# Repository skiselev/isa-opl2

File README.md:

# isa-opl2

ISA OPL2 Card

## Introduction

ISA OPL2 Card is a sound card based on Yamaha OPL2 chip, officially known as YM3812. This card is compatible with the AdLib Music Synthesizer Card that was very popular in late 80's - early 90's.

## Hardware Documentation

### Schematic and PCB Layout

[Schematic - Version 1.2](KiCad/ISA_OPL2-Schematic-1.2.pdf)

[PCB Layout - Version 1.2](KiCad/ISA_OPL2-Board-1.2.pdf)

### Bill of Materials

Component Type     | Reference  | Description                                                | Quantity | Possible Sources and Notes
------------------ | ---------- | ---------------------------------------------------------- | -------- | --------------------------
PCB                |            | ISA OPL2 Version 1.2 PCB                                   | 1        | [Todd Goodman](https://retrobrewcomputers.org/doku.php?id=boardinventory) or your favorite PCB manufacturer
Integrated Circuit | U1         | 74LS245                                                    | 1        | Mouser 595-SN74LS245N
Integrated Circuit | U2, U3     | 74LS138                                                    | 2        | Mouser 595-SN74LS138N
Integrated Circuit | U4         | 74LS74                                                     | 1        | Mouser 595-SN74LS74AN
Integrated Circuit | U5         | 74LS04                                                     | 1        | Mouser 595-SN74LS04N
Integrated Circuit | U6         | YM3812                                                     | 1        | eBay
Integrated Circuit | U7         | YM3014B                                                    | 1        | eBay
Integrated Circuit | U8         | RC4136                                                     | 1        | Mouser 595-RC4136N
Integrated Circuit | U9         | LM386-3                                                    | 1        | Mouser 926-LM386N-3/NOPB
Transistor         | Q1         | 2N3904                                                     | 1        | Mouser 512-2N3904TA
Diode              | D1         | 1N4148                                                     | 1        | Mouser 512-1N4148
Capacitor          | C1 - C11   | 0.1 uF ceramic, 5.08 mm pitch                              | 11       | Mouser 810-FK28X7R1H104K
Capacitor          | C12 - C17  | 10 uF, 16V, multilayer ceramic or tantalum, 5.08 mm pitch  | 6        | Mouser 810-FK24X5R1C106K
Capacitor          | C18        | 220 uF, 16V, electrolytic, axial, 16 mm x 8 mm             | 1        | Mouser 647-TVX1C221MAD
Capacitor          | C19        | 4.7 uF, 16V, multilayer ceramic or tantalum, 5.08 mm pitch | 1	       | Mouser 810-FK24X7R1C475K
Capacitor          | C20        | 47nF, ceramic, 5.08 mm pitch                               | 1        | Mouser 810-FK24X7R2A473K 
Capacitor          | C21 - C24  | 4.7 nF, ceramic, 5.08 mm pitch                             | 4        | Mouser 810-FK28X7R1H472K
Capacitor          | C25        | 1 nF, ceramic, 5.08 mm pitch                               | 1        | Mouser 810-FK28C0G2A102J
Capacitor          | C26        | 270 pF, ceramic, 5.08  mm pitch                            | 1        | Mouser 810-FK28C0G2A271J
Resistor           | R1         | 12 k, 1/4 W                                                | 1        | Mouser 291-12K-RC
Resistor           | R2 - R5    | 10 k, 1/4 W                                                | 4        | Mouser 291-10K-RC
Resistor           | R6         | 8.2 k, 1/4 W                                               | 1        | Mouser 291-8.2K-RC
Resistor           | R7 - R13   | 2.2 k, 1/4 W                                               | 7        | Mouser 291-2.2K-RC
Resistor           | R14        | 1.5 k, 1/4 W                                               | 1        | Mouser 291-1.5K-RC
Resistor           | R15 - R17  | 10 ohm, 1/4 W                                              | 3        | Mouser 291-10-RC
Potentiometer      | RV1        | 10 k, audio, Bourns 91A1A-B24-D15L                         | 1        | Mouser 652-91A1A-B24-D15L
Connector          | J1         | Audio Connector 3.5mm, Stereo                              | 1        | Mouser STX-3120-3B-577C
IC Socket          | U7, U9     | 8 pin 300 mil DIP socket                                   | 2        | Mouser 517-4808-3000-CP
IC Socket          | U4, U5, U8 | 14 pin 300 mil DIP socket                                  | 3        | Mouser 517-4814-3000-CP
IC Socket          | U2, U3     | 16 pin 300 mil DIP socket                                  | 2        | Mouser 517-4816-3000-CP
IC Socket          | U1         | 20 pin 300 mil DIP socket                                  | 1        | Mouser 517-4820-3000-CP
IC Socket          | U6         | 24 pin 600 mil DIP socket                                  | 1        | Mouser 517-4824-6000-CP
Bracket            |            | ISA Bracket, Keystone 9202                                 | 1        | Mouser 534-9202
Screw              |            | Screw, 4-40 thread, 1/4" length                            | 2        | Mouser 534-9900

#### Replacement Notes

* 74LS logic ICs can be replaced other TTL or TTL-compatible CMOS ICs. For example these from 74ALS, 74F, 74AHCT, 74HCT, 74ACT series.
* 1/8 W resistors can be used. It is not recommended to use resistors above 1/4 W, as they have larger packages, and won't easily fit in the board.

### Construction Notes

The ISA OPL2 is relatively easy to build, and most components are widely available. YM3012 (OPL2) and YM3014B (DAC-SS) can be more tricky to get, but they are available on eBay, and from some electronic component suppliers specializing on obsolete components. Please refer to the Bill of Material below for the complete list of components. Also see attached schematic and board layout files on the bottom of this page.

#### Assembling the ISA OPL2 card

* Follow good soldering practices:
  * Clean the board with alcohol before soldering
  * Use solder with flux
  * Keep soldering iron tip clean
  * Apply the minimal amount of solder necessary to fill the hole around the lead

Start with soldering low profile components - diode and resistors
Using needle nose pliers carefully bend resistors' and diode's leads at 90 degrees angle, so that the distance between bended leads is about 7.5mm / 0.3". Be especially careful with the diode, as it is easy to break it by bending leads too close to the package - hold pliers closer to the package, and bend the lead next to the pliers. Pay attention to the diode polarity. The diode has a black stripe that goes around the package, this stripe indicates the cathode, and it should match the orientation of the stripe on the board's silkscreen. The resistors have different resistance marked by the color codes - Google it if you are not familiar with these codes.

Continue with the capacitors (except of C18). If you are using polarized (electrolytic or tantalum) capacitors, pay attention to their polarity. Electrolytic capacitors usually have a stripe with minus (-) signs that indicate the negative lead, the board has positive pin marked with (+). Tantalum capacitors usually have a small plus (+) sign near the positive lead. Capacitance is usually marked explicitly on electrolytic capacitors (e.g. 10 uF), while ceramic and tantalum capacitors use exponential notation in format NNE. To calculate the capacitance use NN * 10 ^ E formula. For example 104 means 10 * 10 ^ 4 = 100,000 pF or 0.1 uF.

Solder the Q1 transistor, make sure it is oriented correctly (package matches the drawing on the silk screen).

Next solder IC sockets (or ICs directly if you're brave). Pay attention to the sockets/ICs orientation. The first lead is marked on the silkscreen with a notch. Sockets usually have similar notch, ICs might have either notch or dot near 1 pin or frequently both of them. I usually solder two opposite pins first while applying slight pressure to the socket/IC so it sits firmly on the board. Then I check that socket/IC is indeed oriented correctly (in case it is not oriented correctly, it is not very difficult to desolder it at this stage), and solder the rest of pins.

Finally solder taller components - C18 capacitor, headphone socket J1, and the potentiometer RV1.

Carefully inspect all solder joins. Resolder any missing or questionable joins.

It is recommended to clean the flux from the finished board with alcohol. I use a toothpick to remove the excessive flux, and the 91% rubbing/isopropyl alcohol, and an old toothbrush to clean the board. Let the alcohol to dry before continuing.

If using sockets - insert ICs to sockets at this stage. Pay attention to the ICs orientation. It is usually necessary to bend IC pins a bit, so they will fit in the socket. Do that by gently pressing ICs against a firm surface (table, ruler). If you overbend them, use a metal ruler to bend them back by placing the ruler between pins and the package, pressing the ruler against a firm surface and applying a slight pressure to the package.

#### Drilling the mounting bracket

First measure and mark holes' positions with a permanent marker or a metal scriber. Next use a center punch or a large screw with pointy tip and a small hammer to mark holes' centers. Place the bracket on a piece of wood, and secure it with a clamp. Start drilling with a small drill diameter gradually increasing the drill diameter. Use low speed then drilling larger diameters, do not apply to much pressure, or the bracket will bend. The final diameter should be about 7 mm - 8 mm (5/16") for both holes.

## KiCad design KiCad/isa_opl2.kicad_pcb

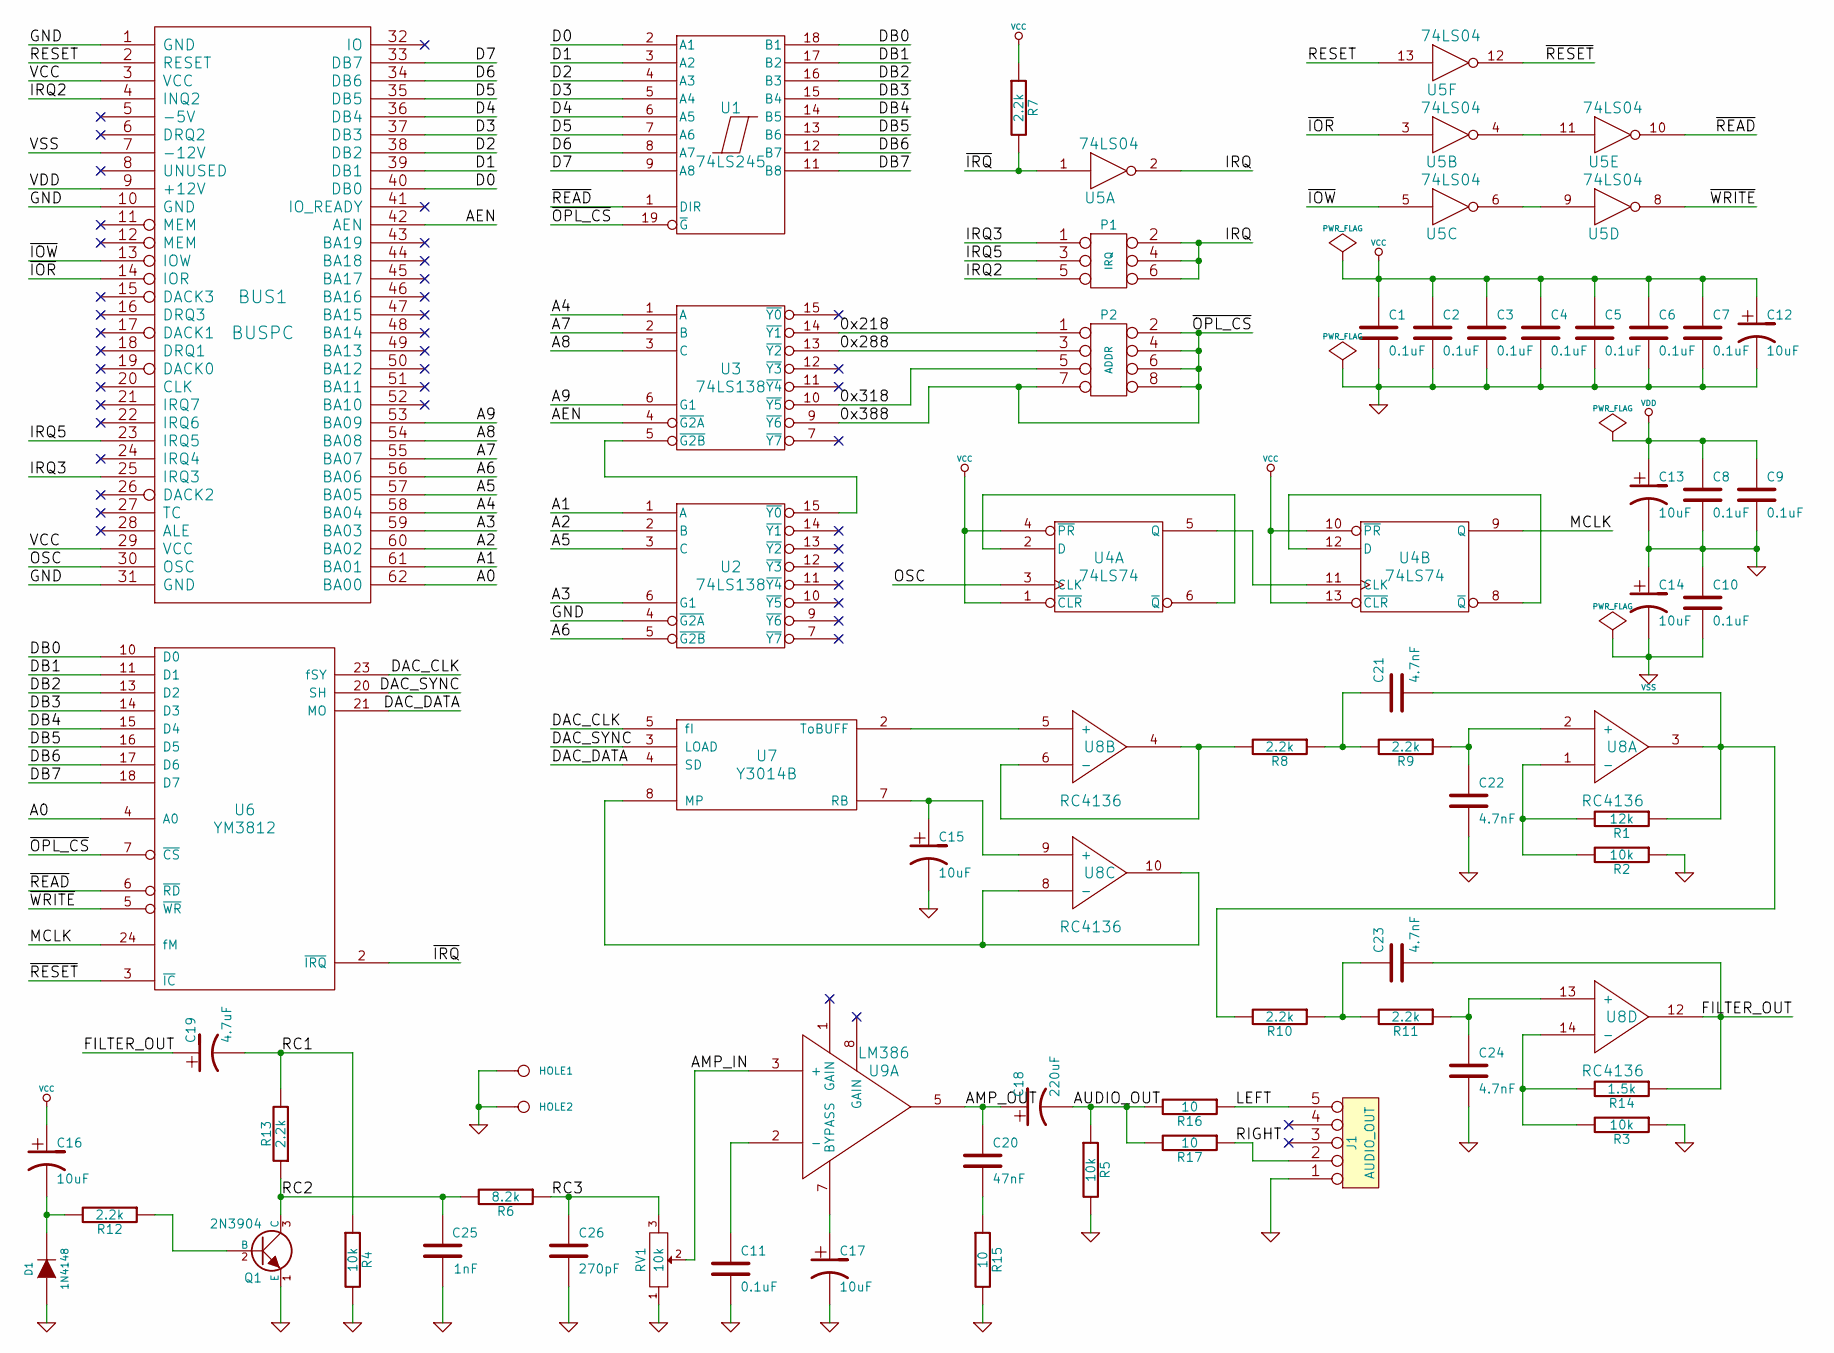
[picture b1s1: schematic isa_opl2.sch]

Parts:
BUS1: BUSPC
C1, C2, C3, C4, C5, C6, C7, C8, C9, C10, C11: 0.1uF
C12, C13, C14, C15, C16, C17: 10uF
C18: 220uF
C19: 4.7uF
C20: 47nF
C21, C22, C23, C24: 4.7nF
C25: 1nF
C26: 270pF
D1: 1N4148
HOLE1, HOLE2: CONN_1
J1: AUDIO_OUT
P1: IRQ
P2: ADDR
Q1: 2N3904
R1: 12k
R2, R3, R4, R5: 10k
R6: 8.2k
R7, R8, R9, R10, R11, R12, R13: 2.2k
R14: 1.5k
R15, R16, R17: 10
RV1: 10k
U1: 74LS245
U2, U3: 74LS138
U4: 74LS74
U5: 74LS04
U6: YM3812
U7: Y3014B
U8: RC4136
U9: LM386

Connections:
/0x218: P2.1, U3.14 (~Y1)
/0x288: P2.3, U3.13 (~Y2)
/0x318: P2.5, U3.10 (~Y5)
/0x388: P2.2, P2.4, P2.6, P2.7, P2.8, U1.19 (~G), U3.9 (~Y6), U6.7 (~CS)
/A0: BUS1.62 (BA00), U6.4 (A0)
/A1: BUS1.61 (BA01), U2.1 (A)
/A2: BUS1.60 (BA02), U2.2 (B)
/A3: BUS1.59 (BA03), U2.6 (G1)
/A4: BUS1.58 (BA04), U3.1 (A)
/A5: BUS1.57 (BA05), U2.3 (C)
/A6: BUS1.56 (BA06), U2.5 (~G2B)
/A7: BUS1.55 (BA07), U3.2 (B)
/A8: BUS1.54 (BA08), U3.3 (C)
/A9: BUS1.53 (BA09), U3.6 (G1)
/AEN: BUS1.42 (AEN), U3.4 (~G2A)
/AMP_IN: RV1.2, U9.3 (+)
/AMP_OUT: C18.1, C20.1, U9.5
/AUDIO_OUT: C18.2, R5.1, R16.2, R17.2
/D0: BUS1.40 (DB0), U1.2 (A1)
/D1: BUS1.39 (DB1), U1.3 (A2)
/D2: BUS1.38 (DB2), U1.4 (A3)
/D3: BUS1.37 (DB3), U1.5 (A4)
/D4: BUS1.36 (DB4), U1.6 (A5)
/D5: BUS1.35 (DB5), U1.7 (A6)
/D6: BUS1.34 (DB6), U1.8 (A7)
/D7: BUS1.33 (DB7), U1.9 (A8)
/DAC_CLK: U6.23 (fSY), U7.5 (fI)
/DAC_DATA: U6.21 (MO), U7.4 (SD)
/DAC_SYNC: U6.20 (SH), U7.3 (LOAD)
/DB0: U1.18 (B1), U6.10 (D0)
/DB1: U1.17 (B2), U6.11 (D1)
/DB2: U1.16 (B3), U6.13 (D2)
/DB3: U1.15 (B4), U6.14 (D3)
/DB4: U1.14 (B5), U6.15 (D4)
/DB5: U1.13 (B6), U6.16 (D5)
/DB6: U1.12 (B7), U6.17 (D6)
/DB7: U1.11 (B8), U6.18 (D7)
/FILTER_OUT: C19.1, C23.2, R14.1, U8.12
/IRQ: P1.2, P1.4, P1.6, U5.2
/IRQ2: BUS1.4 (INQ2), P1.5
/IRQ3: BUS1.25 (IRQ3), P1.1
/IRQ5: BUS1.23 (IRQ5), P1.3
/LEFT: J1.5, R16.1
/MCLK: U4.9 (Q), U6.24 (fM)
/OSC: BUS1.30 (OSC), U4.3 (CLK)
/RC1: C19.2, R4.1, R13.2
/RC2: C25.2, Q1.3 (C), R6.2, R13.1
/RC3: C26.1, R6.1, RV1.3
/RESET: BUS1.2 (RESET), U5.13
/RIGHT: J1.2, R17.1
/~IOR: BUS1.14 (IOR), U5.3
/~IOW: BUS1.13 (IOW), U5.5
/~IRQ: R7.2, U5.1, U6.2 (~IRQ)
/~READ: U1.1 (DIR), U5.10, U6.6 (~RD)
/~RESET: U5.12, U6.3 (~IC)
/~WRITE: U5.8, U6.5 (~WR)
GND: BUS1.1 (GND), BUS1.10 (GND), BUS1.31 (GND), C1.2, C2.2, C3.2, C4.2, C5.2, C6.2, C7.2, C8.2, C9.2, C10.1, C11.2, C12.2, C13.2, C14.1, C15.2, C17.2, C22.2, C24.2, C25.1, C26.2, D1.1 (A), HOLE1.1, HOLE2.1, J1.1, Q1.1 (E), R2.1, R3.1, R4.2, R5.2, R15.2, RV1.1, U1.10 (GND), U2.4 (~G2A), U2.8 (GND), U3.8 (GND), U4.7 (GND), U5.7 (GND), U6.12 (GND), U7.6 (GND), U9.4 (GND)
unnamed: C11.1, U9.2 (-)
unnamed: C15.1, U7.7 (RB), U8.9 (+)
unnamed: C16.2, D1.2 (K), R12.2
unnamed: C17.1, U9.7 (BYPASS)
unnamed: C20.2, R15.1
unnamed: C21.1, R8.1, R9.2
unnamed: C21.2, R1.1, R10.2, U8.3
unnamed: C22.1, R9.1, U8.2 (+)
unnamed: C23.1, R10.1, R11.2
unnamed: C24.1, R11.1, U8.13 (+)
unnamed: Q1.2 (B), R12.1
unnamed: R1.2, R2.2, U8.1 (-)
unnamed: R8.2, U8.4, U8.6 (-)
unnamed: R3.2, R14.2, U8.14 (-)
unnamed: U2.15 (~Y0), U3.5 (~G2B)
unnamed: U4.2 (D), U4.6 (~Q)
unnamed: U4.5 (Q), U4.11 (CLK)
unnamed: U4.8 (~Q), U4.12 (D)
unnamed: U5.6, U5.9
unnamed: U5.4, U5.11
unnamed: U7.2 (ToBUFF), U8.5 (+)
unnamed: U7.8 (MP), U8.8 (-), U8.10
VCC: BUS1.3 (VCC), BUS1.29 (VCC), C1.1, C2.1, C3.1, C4.1, C5.1, C6.1, C7.1, C12.1, C16.1, R7.1, U1.20 (VCC), U2.16 (VCC), U3.16 (VCC), U4.1 (~CLR), U4.4 (~PR), U4.10 (~PR), U4.13 (~CLR), U4.14 (VCC), U5.14 (VCC), U6.1 (VCC), U7.1 (VCC)
VDD: BUS1.9 (+12V), C8.1, C9.1, C13.1, U8.11 (VDD), U9.6 (VDD)
VSS: BUS1.7 (-12V), C10.2, C14.2, U8.7 (VSS)

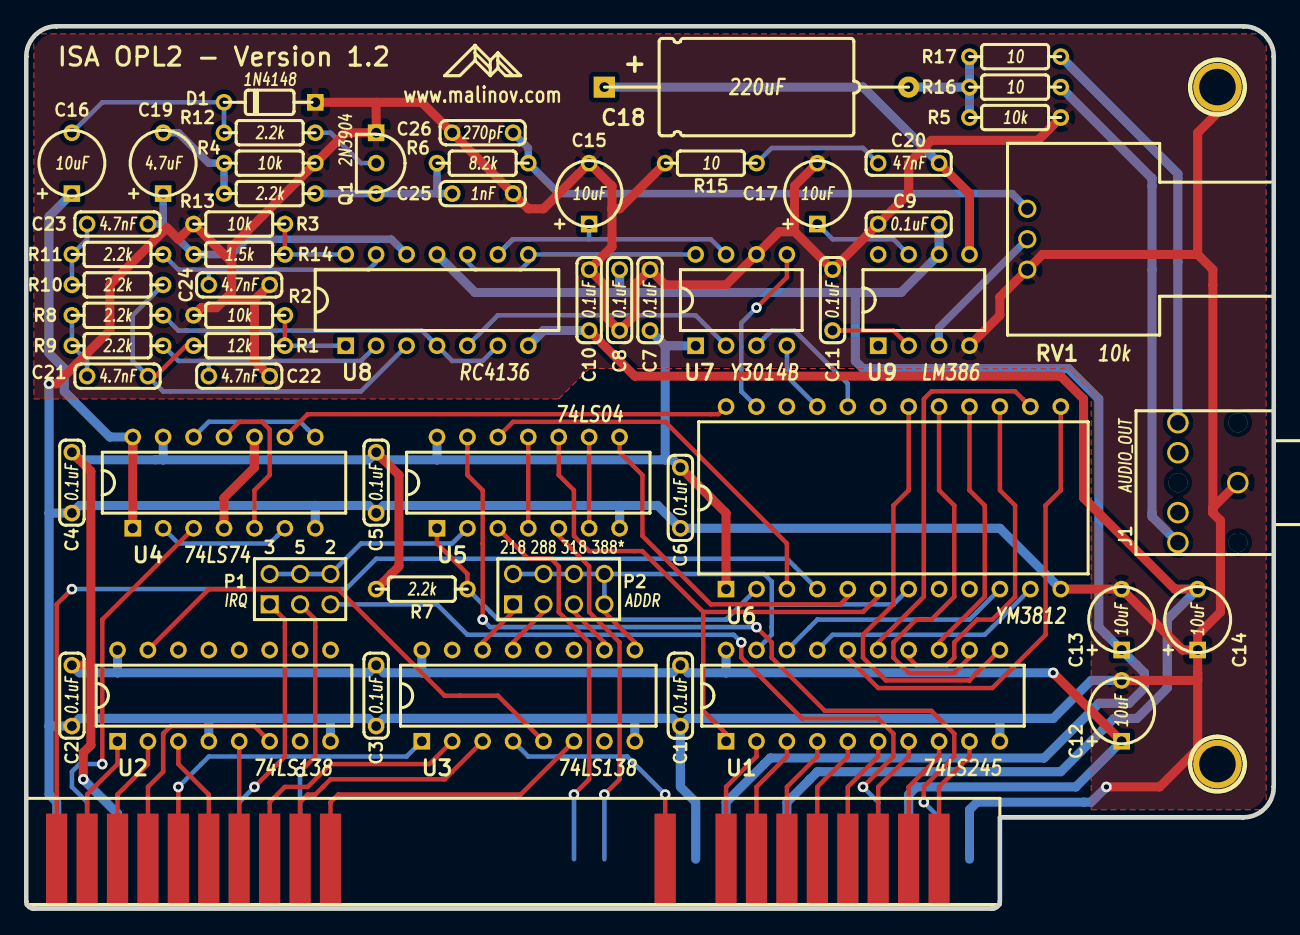
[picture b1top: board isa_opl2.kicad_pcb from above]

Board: 2 copper layers, 104.1 x 73.7 mm, 61 parts (0 on the bottom side), 82 nets.

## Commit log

2023-10-31 Add v0.9 files
2023-10-31 Add v1.0 files
2023-10-31 Add v1.2 files
